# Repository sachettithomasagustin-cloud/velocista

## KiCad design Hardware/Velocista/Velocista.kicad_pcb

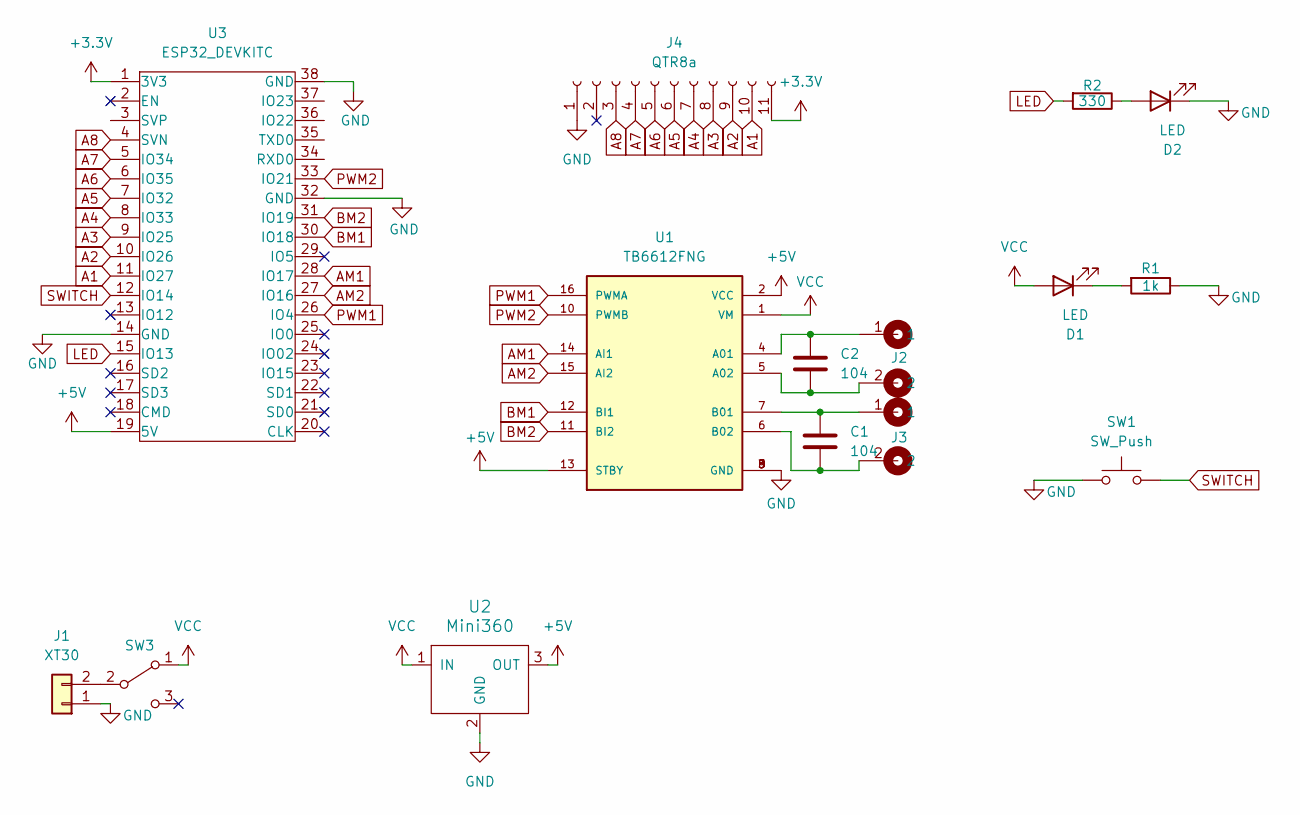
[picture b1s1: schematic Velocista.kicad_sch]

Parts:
C1, C2: 104; C_Disc_D5.0mm_W2.5mm_P2.50mm
D1, D2: LED; led_5mm_green
J1: XT30; AMASS_XT30UPB-M_1x02_P5.0mm_Vertical
J2, J3: Cable_PAD; Cable-doble-THT
J4: QTR8a; JST_EH_S11B-EH_1x11_P2.50mm_Horizontal
R1: 1k; R_0805_2012Metric_Pad1.20x1.40mm_HandSolder
R2: 330; R_0805_2012Metric_Pad1.20x1.40mm_HandSolder
SW1: SW_Push; SW_PUSH_1P1T_6x3.5mm_H5.0_APEM_MJTP1250
SW3: SW_SPDT; SW_EG1247
U1: TB6612FNG; MODULE_ROB-14450; PARTREV 11-13-17
U2: Mini360; Mini360_step-down
U3: ESP32_DEVKITC; ESP32S

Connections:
+3.3V: J4.11, U3.1 (3V3)
+5V: U1.2 (VCC), U1.13 (STBY), U2.3 (OUT), U3.19 (5V)
A1: J4.10, U3.11 (IO27)
A2: J4.9, U3.10 (IO26)
A3: J4.8, U3.9 (IO25)
A4: J4.7, U3.8 (IO33)
A5: J4.6, U3.7 (IO32)
A6: J4.5, U3.6 (IO35)
A7: J4.4, U3.5 (IO34)
A8: J4.3, U3.4 (SVN)
AM1: U1.14 (AI1), U3.28 (IO17)
AM2: U1.15 (AI2), U3.27 (IO16)
BM1: U1.12 (BI1), U3.30 (IO18)
BM2: U1.11 (BI2), U3.31 (IO19)
GND: D2.1 (K), J1.1, J4.1, R1.1, SW1.1, U1.3 (GND), U1.8 (GND), U1.9 (GND), U2.2 (GND), U3.14 (GND), U3.32 (GND), U3.38 (GND)
LED: R2.2, U3.15 (IO13)
unnamed: D1.1 (K), R1.2
unnamed: D2.2 (A), R2.1
unnamed: J1.2, SW3.2 (B)
unnamed: C2.1, J2.1, U1.4 (A01)
unnamed: C2.2, J2.2, U1.5 (A02)
unnamed: C1.2, J3.1, U1.7 (B01)
unnamed: C1.1, J3.2, U1.6 (B02)
PWM1: U1.16 (PWMA), U3.26 (IO4)
PWM2: U1.10 (PWMB), U3.33 (IO21)
SWITCH: SW1.2, U3.12 (IO14)
VCC: D1.2 (A), SW3.1 (A), U1.1 (VM), U2.1 (IN)

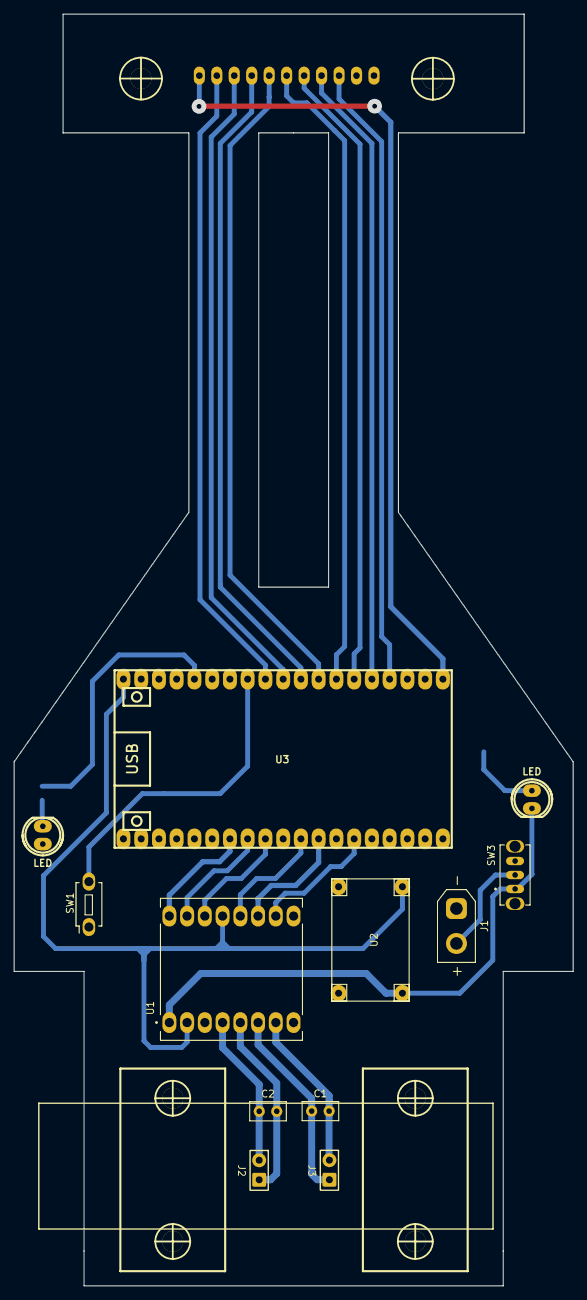
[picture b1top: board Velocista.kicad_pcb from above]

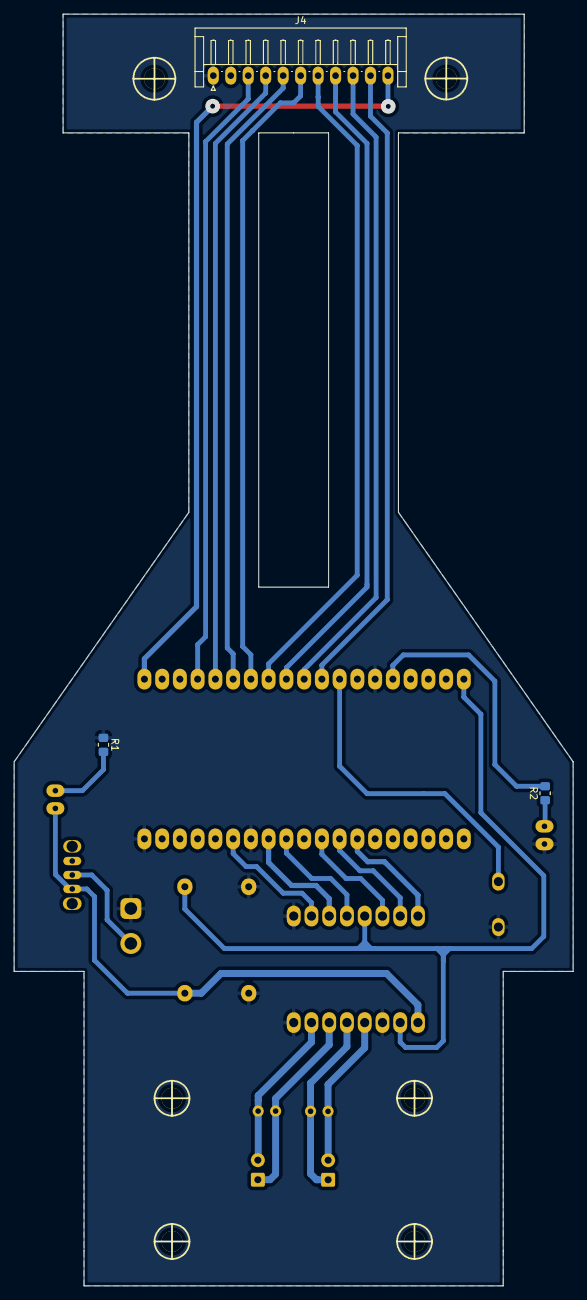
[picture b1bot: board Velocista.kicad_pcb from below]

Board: 2 copper layers, 80.0 x 182.0 mm, 19 parts (3 on the bottom side), 27 nets.

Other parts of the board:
Pololu_Micro_Gear_Motor: VAL**; Pololu_Micro_Bracket_Wheel_42mm
Pololu_Micro_Gear_Motor#2: VAL**; Pololu_Micro_Bracket_Wheel_42mm
Tornillo_M3_8mm, Tornillo_M3_8mm#2: VAL**; Tornillo_M3_8mm

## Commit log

2026-03-27 mi primer commit
2026-03-27 modificamos titulo en index.html
2026-03-27 se agregaron nuevas carpetas
2026-04-07 Se añade el proyecto
2026-04-07 Se borraron carpetas viejas
2026-04-13 se sube el proyecto
2026-04-13 act proyecto
2026-04-13 actualizacion
2026-04-21 Act hardware
2026-04-21 README.md
